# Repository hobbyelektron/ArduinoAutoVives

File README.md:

# ArduinoAutoVives
Arduino Auto Vives

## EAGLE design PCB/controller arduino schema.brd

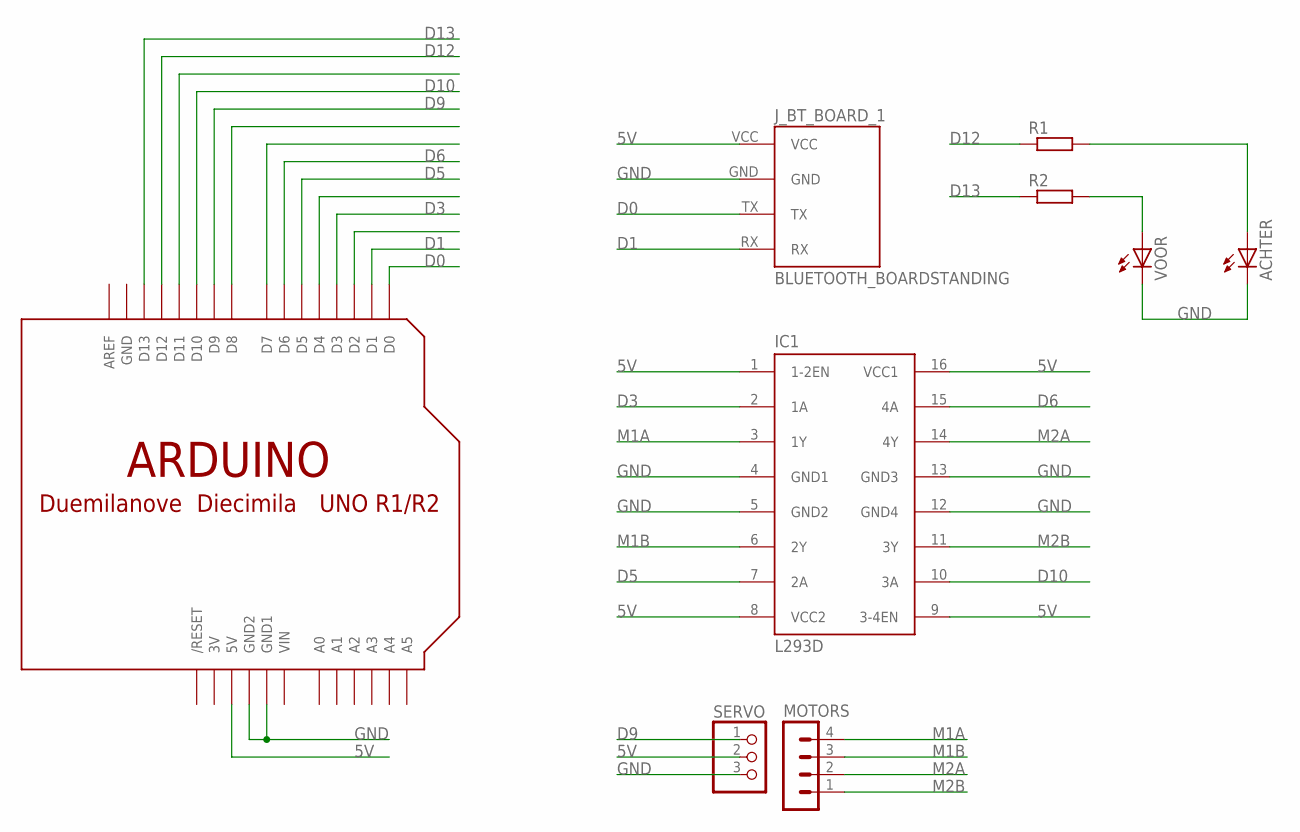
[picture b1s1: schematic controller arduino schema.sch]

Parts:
ACHTER: LED5MM
IC1: L293D; DIL16
J_BT_BOARD_1: BLUETOOTH_BOARDSTANDING; BT_BOARD_FOOTPRINT_STANDING
MOTORS: MA04-1
R1, R2: R-EU_0207/7; 0207/7
SERVO: PINHD-1X3; 1X03
U$1: ARDUINO-BPLACE
VOOR: LED5MM

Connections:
3V: U$1.3V
5V: IC1.1 (1-2EN), IC1.8 (VCC2), IC1.9 (3-4EN), IC1.16 (VCC1), J_BT_BOARD_1.VCC, SERVO.2, U$1.5V
D0: J_BT_BOARD_1.TX, U$1.D0
D1: J_BT_BOARD_1.RX, U$1.D1
D3: IC1.2 (1A), U$1.D3
D5: IC1.7 (2A), U$1.D5
D6: IC1.15 (4A), U$1.D6
D9: SERVO.1, U$1.D9
D10: IC1.10 (3A), U$1.D10
D12: R1.1, U$1.D12
D13: R2.1, U$1.D13
GND: ACHTER.K (C), IC1.4 (GND1), IC1.5 (GND2), IC1.12 (GND4), IC1.13 (GND3), J_BT_BOARD_1.GND, SERVO.3, U$1.GND, U$1.GND1, U$1.GND2, VOOR.K (C)
M1A: IC1.3 (1Y), MOTORS.4
M1B: IC1.6 (2Y), MOTORS.3
M2A: IC1.14 (4Y), MOTORS.2
M2B: IC1.11 (3Y), MOTORS.1
unnamed: R2.2, VOOR.A
unnamed: ACHTER.A, R1.2
VIN: U$1.VIN

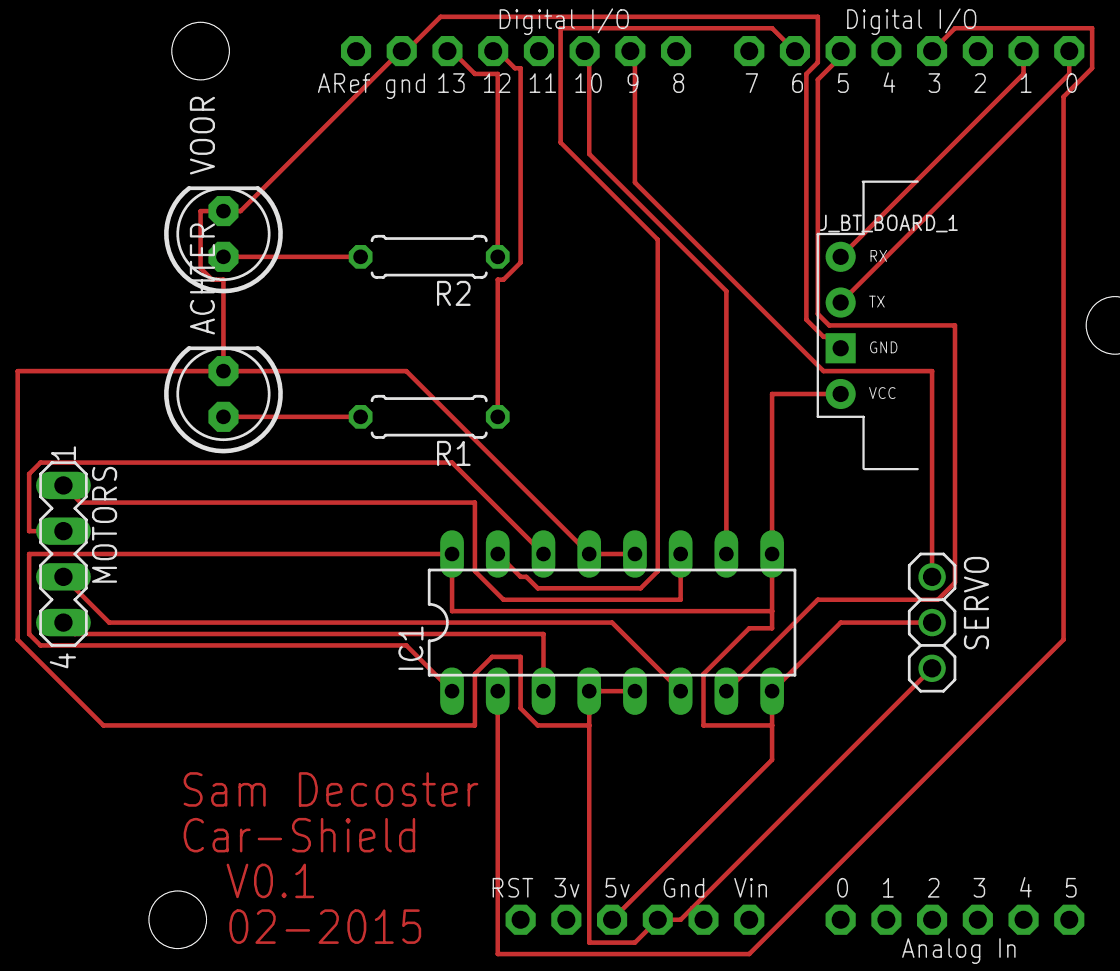
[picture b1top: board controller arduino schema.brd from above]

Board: 2 copper layers, 9 parts (0 on the bottom side), 17 nets.

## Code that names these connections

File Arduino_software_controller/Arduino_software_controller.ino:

//Include servo library
#include <Servo.h> 

/*
byte array:
  0. Vooruit
  1. Achteruit
  2. Links
  3. Rechts
  4. Lichten
  5. Servo
*/
byte Input[6]; //aanmaken van byte array met 6 bytes

//declareren en initialiseren van motor uitgang variabelen
int M1A = 3;
int M1B = 5;
int M2A = 6;
int M2B = 10;

//aanmaken servo object "myservo"
Servo myservo;

//declareren positie van servo standaard is 0°
int Spos = 0;

//declareren en initialiseren van lichten uitgang variabelen
int Voorlicht = 13; //Voorlicht op pin 13
int Achterlicht = 12; //Achterlicht op pin 12


//start van de Setup lus
void setup() {
  //starten van seriele verbinding met baud rate van 9600
  Serial.begin(9600);
  
  //lichten als uitgang definieren
  pinMode(Voorlicht, OUTPUT);  //Voorlicht als uitgang
  pinMode(Achterlicht, OUTPUT); //Achterlicht als uitgang
  
  //standaard alle lichten uit
  digitalWrite(Voorlicht, LOW);
  digitalWrite(Achterlicht, LOW);
  
  //"myservo" object toekenen aan pin 9
  myservo.attach(9);
  
  //motors toekenen als uitgang
  pinMode(M1A, OUTPUT);
  pinMode(M1B, OUTPUT);
  pinMode(M2A, OUTPUT);
  pinMode(M2B, OUTPUT);
  
  //standaard bij opstart motoren uit!
  digitalWrite(M1A, LOW);
  digitalWrite(M1B, LOW);
  digitalWrite(M2A, LOW);
  digitalWrite(M2B, LOW);
  analogWrite(M1A, 0);
  analogWrite(M1B, 0);
  analogWrite(M2A, 0);
  analogWrite(M2B, 0);
}
//einde van de Setup lus


//starten van de Loop lus
void loop() {
  // kijken of er seriele communicatie is?
  if(Serial.available()){
    //Als er seriele communicatie is:
    //lezen van de seriele input (6bytes 0->5)
    Serial.readBytes(Input, 6); //6 staat voor 6bytes; Input staat voor de array variabele
    
    //sturen van de motors
    //de controlles diennen voor analogWrite niet werkt door Servo library
    //sturen van motor M1A
    if (Input[0] == 255){
      analogWrite(M1A, 0); // M1A Analoog op 0
      digitalWrite(M1A, HIGH); // M1A HIGH
    }
    else{
      digitalWrite(M1A, LOW); // M1A LOW
      analogWrite(M1A, Input[0]); //sturen M1A Analoog
    }
    
    //sturen van motor M1B
    if (Input[1] == 255){
      analogWrite(M1B, 0); // M1B Analoog op 0
      digitalWrite(M1B, HIGH); // M1B HIGH
    }
    else{
      digitalWrite(M1B, LOW); // M1B LOW
      analogWrite(M1B, Input[1]); //sturen M1B Analoog
    }
    
    //sturen van motor M2A
    if (Input[2] == 255){
      analogWrite(M2A, 0); // M2A Analoog op 0
      digitalWrite(M2A, HIGH); // M2A HIGH
    }
    else{
      digitalWrite(M2A, LOW); // M2A LOW
      analogWrite(M2A, Input[2]); //sturen M2A Analoog
    }
    
    //sturen van motor M2B
    if (Input[3] == 255){
      analogWrite(M2B, 0); // M2B Analoog op 0
      digitalWrite(M2B, HIGH); // M2B HIGH
    }
    else{
      digitalWrite(M2B, LOW); // M2B LOW
      analogWrite(M2B, Input[3]); //sturen M2B Analoog
    }
    
    //sturen van de led's
    //controlleren van Input[4]
    if (Input[4] == 0){
      //alle lampen UIT!
      digitalWrite(Voorlicht, LOW);
      digitalWrite(Achterlicht, LOW);
    }
    else if (Input[4] == 1){
      //Voorlicht AAN, Achterlicht UIT
      digitalWrite(Voorlicht, HIGH);
      digitalWrite(Achterlicht, LOW);
    }
    else if (Input[4] == 2){
      //Voorlicht UIT, Achterlicht AAN
      digitalWrite(Voorlicht, LOW);
      digitalWrite(Achterlicht, HIGH);
    }
    else if (Input[4] == 3){
      //alle lampen AAN!
      digitalWrite(Voorlicht, HIGH);
      digitalWrite(Achterlicht, HIGH);
    }
      
    //einde controlle lampen
    
    //controlleren van servo ingang
    if (Input[5] > 180){
      //indien hoek groter is dan 180° wordt de servo op 180°geplaatst
      Spos = 180;
    }
    else{
      //indien de hoek niet groter is dan 180° wordt de ingang[5] gebruikt als hoek
      Spos = Input[5];
    }
    //einde controlleren van de servo uitgang
    
    //sturen van de servo
    myservo.write(Spos); //voor waarde Spos zie controlle hierboven
  }
  // einde kijken of er seriele communicatie is?
}
//einde van de Loop lus

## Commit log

2015-04-12 Update LICENSE
2015-04-12 Add Arduino Software for car
2015-04-12 Add PCB file's
2015-04-12 Update LICENSE
    add e-mail of Sam
2015-04-12 Update LICENSE
    add mail of jasper opzomer
2015-04-12 Update LICENSE
    add another hardware developer
2015-04-12 Add PC software C#
2015-04-12 Add hardware documentation
2015-04-15 Add code for Drive left/right
2015-04-15 Add icon
2015-04-15 add code for max and min size
2015-04-17 update Stop button for left and right
2015-04-19 dwengo change
